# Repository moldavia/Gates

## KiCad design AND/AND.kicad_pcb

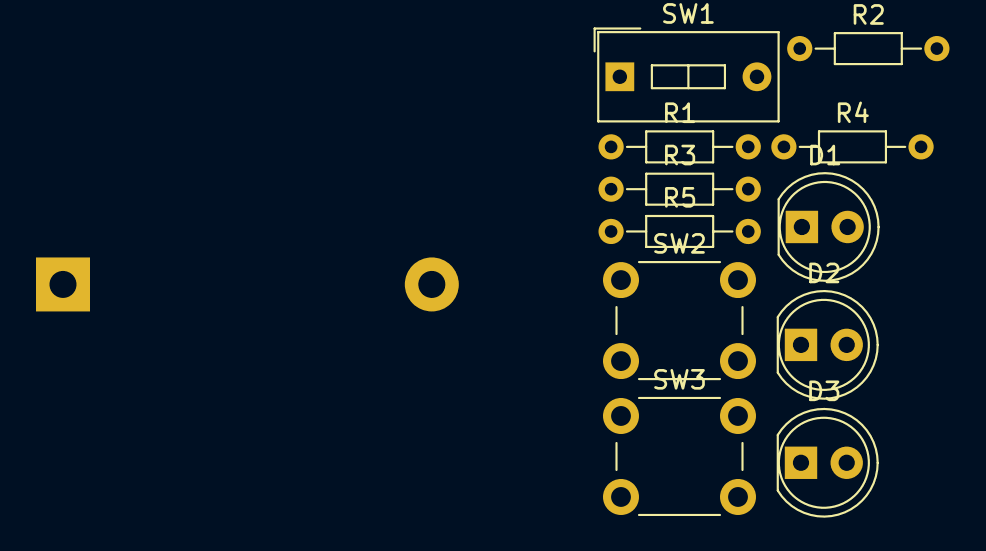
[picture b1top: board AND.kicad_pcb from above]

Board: 2 copper layers, 12 parts (1 on the bottom side), 8 nets, no tracks yet.

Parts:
BT1: Battery_Cell; Keystone_106_1x20mm-CoinCell
D1, D2, D3: LED_ALT; LED_D5.0mm
R1, R2, R5: 100R; R_Axial_DIN0204_L3.6mm_D1.6mm_P7.62mm_Horizontal
R3, R4: 10kR; R_Axial_DIN0204_L3.6mm_D1.6mm_P7.62mm_Horizontal
SW1: SW_SPST; SW_DIP_x1_W7.62mm_Slide
SW2, SW3: SW_SPST; SW_PUSH_6mm

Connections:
GNDREF: BT1.2, D1.1, D2.1, D3.1
unnamed: BT1.1, SW1.1
unnamed: D1.2, R1.2
unnamed: D2.2, R2.2
unnamed: D3.2, R5.2
unnamed: R1.1, R3.2, SW2.2
unnamed: R2.1, R4.2, SW3.2
VCC: SW1.2, SW2.1, SW3.1

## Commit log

2019-03-08 Initial commit of gates project
2019-03-11 Cleanup, begin AND gate.
